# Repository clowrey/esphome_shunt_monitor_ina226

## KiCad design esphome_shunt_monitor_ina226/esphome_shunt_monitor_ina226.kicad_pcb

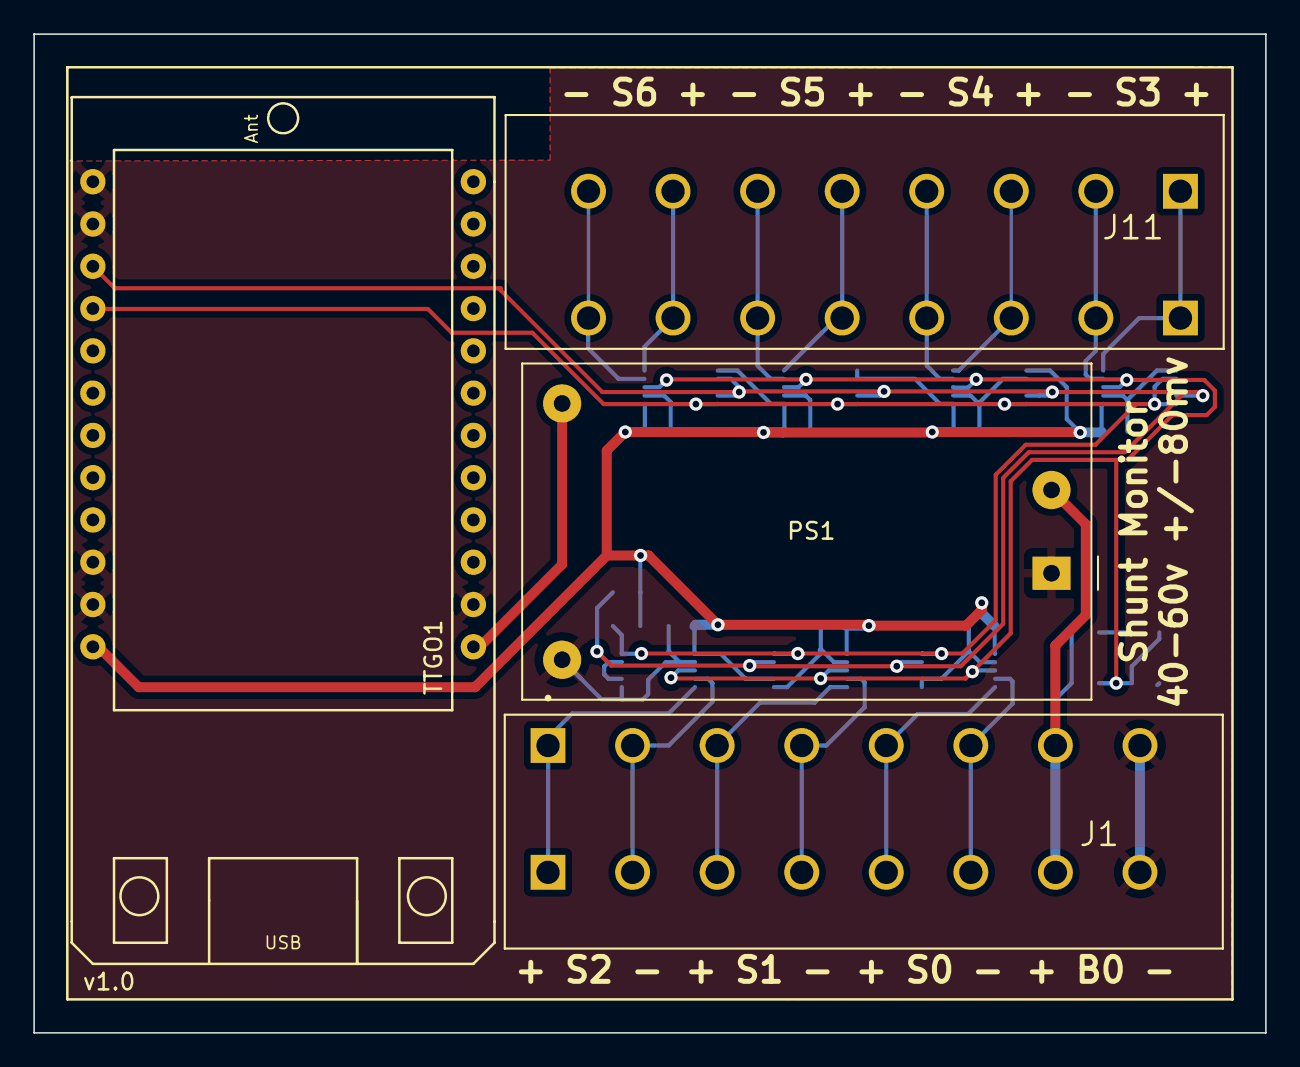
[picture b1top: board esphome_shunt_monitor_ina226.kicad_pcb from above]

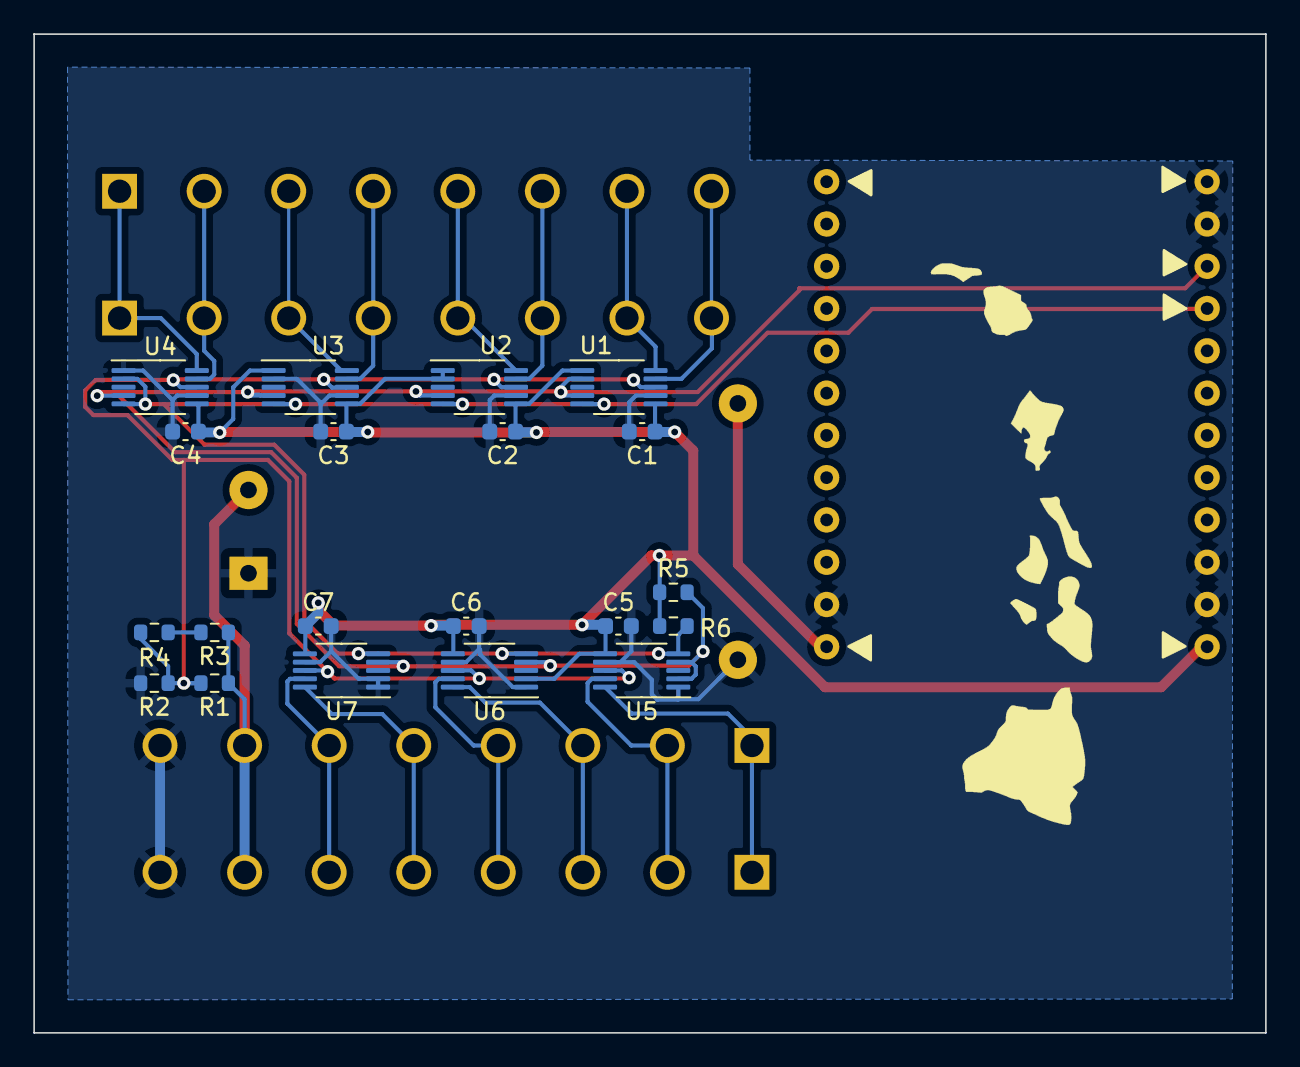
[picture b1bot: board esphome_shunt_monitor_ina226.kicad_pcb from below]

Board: 2 copper layers, 74.0 x 60.0 mm, 24 parts (20 on the bottom side), 22 nets.

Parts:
C1, C2, C3, C4, C5, C6, C7: .1uf; C_0603_1608Metric
J1, J11: TBL004-508-08BE-2BE; CUI_TBL004-508-08BE-2BE
PS1: HLK-PM01; Converter_ACDC_HiLink_HLK-PMxx
R1, R2, R5, R6: 10k; R_0603_1608Metric
R3: 150k; R_0603_1608Metric
R4: 22k; R_0603_1608Metric
TTGO1: TTGO_ESP32_TDISPLAY_V1.1; TTGO_ESP32_TDisplay_v1.1
U1, U2, U3, U4, U5, U6, U7: INA226; VSSOP-10_3x3mm_P0.5mm

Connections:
+3.3V: C1.1, C2.1, C3.1, C4.1, C5.1, C6.1, C7.1, R5.1, R6.1, TTGO1.24 (3.3V), U1.1 (A1), U1.6 (VS), U2.1 (A1), U2.2 (A0), U2.6 (VS), U3.1 (A1), U3.6 (VS), U4.6 (VS), U5.6 (VS), U6.2 (A0), U6.6 (VS), U7.6 (VS)
/5V: PS1.4 (+Vout), TTGO1.1 (5V)
/INA226-0/Vin+: J11.7_A (7), J11.7_B (7), U1.10 (Vin+)
/INA226-0/Vin-: J11.8_A (8), J11.8_B (8), U1.9 (Vin-)
/INA226-1/Vin+: J11.5_A (5), J11.5_B (5), U2.10 (Vin+)
/INA226-1/Vin-: J11.6_A (6), J11.6_B (6), U2.9 (Vin-)
/INA226-2/Vin+: J11.3_A (3), J11.3_B (3), U3.10 (Vin+)
/INA226-2/Vin-: J11.4_A (4), J11.4_B (4), U3.9 (Vin-)
/INA226-3/Vin+: J11.1_A (1), J11.1_B (1), U4.10 (Vin+)
/INA226-3/Vin-: J11.2_A (2), J11.2_B (2), U4.9 (Vin-)
/INA226-4/Vin+: J1.1_A (1), J1.1_B (1), U5.10 (Vin+)
/INA226-4/Vin-: J1.2_A (2), J1.2_B (2), U5.9 (Vin-)
/INA226-5/Vin+: J1.3_A (3), J1.3_B (3), U6.10 (Vin+)
/INA226-5/Vin-: J1.4_A (4), J1.4_B (4), U6.9 (Vin-)
/INA226-6/Vin+: J1.5_A (5), J1.5_B (5), U7.10 (Vin+)
/INA226-6/Vin-: J1.6_A (6), J1.6_B (6), U7.9 (Vin-)
/V+Input: J1.7_A (7), J1.7_B (7), PS1.2 (AC/N), R1.1, R3.1
GND: C1.2, C2.2, C3.2, C4.2, C5.2, C6.2, C7.2, J1.8_A (8), J1.8_B (8), PS1.1 (AC/L), PS1.3 (-Vout), R2.2, TTGO1.2 (GND), TTGO1.13 (GND), TTGO1.14 (GND), TTGO1.22 (GND), TTGO1.23 (GND), U1.7 (GND), U2.7 (GND), U3.2 (A0), U3.7 (GND), U4.1 (A1), U4.7 (GND), U5.1 (A1), U5.7 (GND), U6.1 (A1), U6.7 (GND), U7.1 (A1), U7.2 (A0), U7.7 (GND)
unnamed: R3.2, R4.1
SCL: R6.2, TTGO1.16 (GPIO22), U1.5 (SCL), U2.5 (SCL), U3.5 (SCL), U4.2 (A0), U4.5 (SCL), U5.5 (SCL), U6.5 (SCL), U7.5 (SCL)
SDA: R5.2, TTGO1.15 (GPIO21), U1.2 (A0), U1.4 (SDA), U2.4 (SDA), U3.4 (SDA), U4.4 (SDA), U5.2 (A0), U5.4 (SDA), U6.4 (SDA), U7.4 (SDA)
Vbus: R1.2, R2.1, R4.2, U1.8 (Vbus), U2.8 (Vbus), U3.8 (Vbus), U4.8 (Vbus), U5.8 (Vbus), U6.8 (Vbus), U7.8 (Vbus)

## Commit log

2022-12-27 rev 0 ordered
2023-01-04 update din rail mount
